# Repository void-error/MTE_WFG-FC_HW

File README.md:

# MTE_WFG-FC_HW
Waveform Generator + Frequency Counter hardware

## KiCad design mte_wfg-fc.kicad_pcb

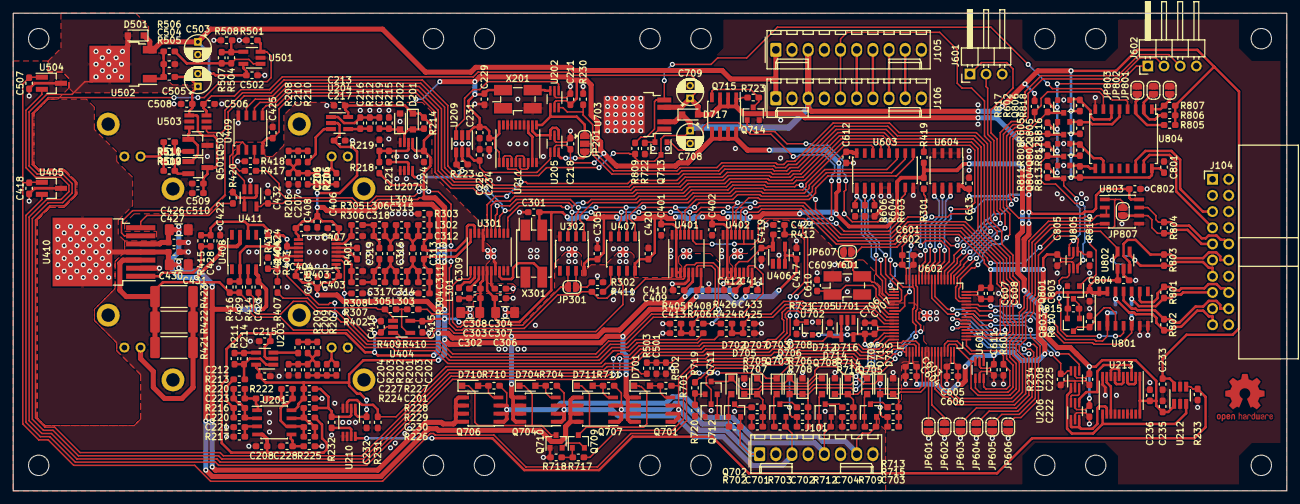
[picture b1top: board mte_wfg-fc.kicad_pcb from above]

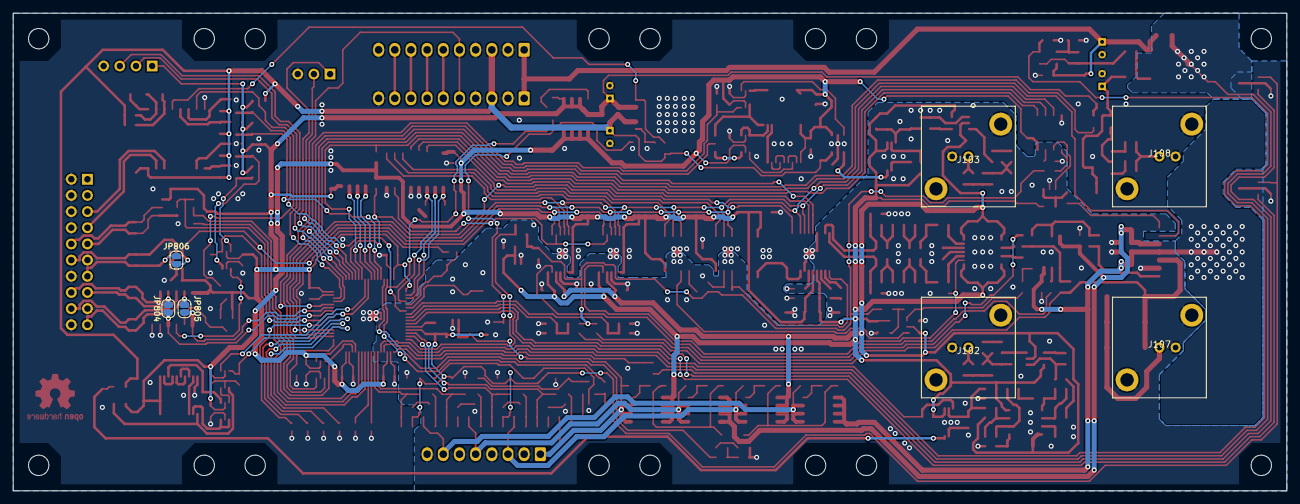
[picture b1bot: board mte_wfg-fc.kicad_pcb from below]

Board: 2 copper layers, 200.0 x 75.0 mm, 395 parts (7 on the bottom side), 222 nets.

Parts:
C201, C208, C211, C212, C213, C215, C217, C218, C222, C224, C225, C226, C229, C231, C232, C233, C234, C235, C236, C301, C303, C305, C307, C401, C402, C403, C404, C407, C408, C409, C410, C411, C412, C414, C415, C416, C418, C420, C422, C423, C425, C427, C430, C432, C502, C506, C507, C508, C509, C602, C603, C605, C607, C611, C612, C613, C801, C802, C803, C804, C805: 100n; C_0603_1608Metric_Pad1.05x0.95mm_HandSolder
C202, C205, C223, C230: 47p; C_0603_1608Metric_Pad1.05x0.95mm_HandSolder
C203, C206, C220, C227: 15p; C_0603_1608Metric_Pad1.05x0.95mm_HandSolder
C204, C207: 100p; C_0603_1608Metric_Pad1.05x0.95mm_HandSolder
C209, C210, C319: 33p; C_0603_1608Metric_Pad1.05x0.95mm_HandSolder
C214, C216, C221, C228, C310, C609, C610: 22p; C_0603_1608Metric_Pad1.05x0.95mm_HandSolder
C219, C304, C308, C309, C501, C701, C702, C703, C704, C707: 10n; C_0603_1608Metric_Pad1.05x0.95mm_HandSolder
C302, C306: 10u; C_1206_3216Metric_Pad1.42x1.75mm_HandSolder
C311, C312, C424, C429: 3p3; C_0603_1608Metric_Pad1.05x0.95mm_HandSolder
C313, C316: 56p; C_0603_1608Metric_Pad1.05x0.95mm_HandSolder
C314, C315: 10p; C_0603_1608Metric_Pad1.05x0.95mm_HandSolder
C317, C318: 6p8; C_0603_1608Metric_Pad1.05x0.95mm_HandSolder
C405, C406, C601, C604, C606, C608: 4u7; C_0603_1608Metric_Pad1.05x0.95mm_HandSolder
C413, C421, C428, C433: 1n; C_0603_1608Metric_Pad1.05x0.95mm_HandSolder
C417, C419, C504, C510, C705, C706: 1u; C_0603_1608Metric_Pad1.05x0.95mm_HandSolder
C426, C431: 1u; C_1206_3216Metric_Pad1.42x1.75mm_HandSolder
C503, C505, C708, C709: 10u; CP_Radial_D4.0mm_P2.00mm
D201, D202, D501, D717: BAS316; D_SOD-323_HandSoldering
D701, D702, D703, D704, D705, D706, D707, D708, D709, D710, D711, D712, D713, D714, D715, D716: BAT54J; D_SOD-323_HandSoldering
J101: MOLEX_KK-254; Molex_KK-254_AE-6410-08A_1x08_P2.54mm_Vertical
J102, J103, J107, J108: CONN_COAXIAL; TE_1-1337541-0
J104: Conn_02x10_Odd_Even; IDC-Header_2x10_P2.54mm_Horizontal
J105, J106: Conn_01x10; Molex_KK-254_AE-6410-10A_1x10_P2.54mm_Vertical
J601: Conn_01x03; PinHeader_1x03_P2.54mm_Horizontal
J602: Conn_01x04; PinHeader_1x04_P2.54mm_Horizontal
JP201: SolderJumper_3_Open; SolderJumper-3_P1.3mm_Open_RoundedPad1.0x1.5mm
JP301, JP601, JP602, JP603, JP604, JP605, JP606, JP607, JP801, JP802, JP803, JP804, JP805, JP806, JP807: SolderJumper_2_Open; SolderJumper-2_P1.3mm_Open_RoundedPad1.0x1.5mm
L301, L302: 3u3; L_0603_1608Metric_Pad1.05x0.95mm_HandSolder
L303, L304, L305, L306: 4u7; L_0603_1608Metric_Pad1.05x0.95mm_HandSolder
LOGO101: OSHW; OSHW-Logo2_9.8x8mm_Copper
MK101, MK102, MK103, MK104, MK105, MK106, MK107, MK108, MK109, MK110, MK111, MK112, MK113, MK114, MK115, MK116: mechanical:Mounting_Hole; MountingHole_3.2mm_M3
NT301, NT401, NT402, NT403, NT404, NT601: Net-Tie_4; NetTie-4_SMD_Pad0.5mm
Q501: BSS315P; SOT-23_Handsoldering
Q502: BSS316N; SOT-23_Handsoldering
Q701, Q707, Q715: IRF7241; SOIC-8_3.9x4.9mm_P1.27mm
Q702, Q708, Q803, Q805: BSS84; SOT-23
Q703, Q705, Q713, Q714, Q801, Q802, Q804, Q806: BSS138; SOT-23
Q704, Q706: IRF7468; SOIC-8_3.9x4.9mm_P1.27mm
Q709, Q711: BC847; SOT-23
Q710, Q712: BC857; SOT-23
R201, R204: 150k; R_0603_1608Metric_Pad1.05x0.95mm_HandSolder
R202, R205, R207, R208: 750; R_0603_1608Metric_Pad1.05x0.95mm_HandSolder
R203, R206, R223, R230, R231, R233, R234, R501, R504, R507, R601, R814: 100k; R_0603_1608Metric_Pad1.05x0.95mm_HandSolder
R209, R210: 150; R_0603_1608Metric_Pad1.05x0.95mm_HandSolder
R211, R212: 300R; R_0603_1608Metric_Pad1.05x0.95mm_HandSolder
R213, R216, R222, R224: 300; R_0603_1608Metric_Pad1.05x0.95mm_HandSolder
R214, R215, R218, R219, R227, R228: 1k5; R_0603_1608Metric_Pad1.05x0.95mm_HandSolder
R217, R225: 470; R_0603_1608Metric_Pad1.05x0.95mm_HandSolder
R220: 1k8; R_0603_1608Metric_Pad1.05x0.95mm_HandSolder
R221, R232, R714: 75k; R_0603_1608Metric_Pad1.05x0.95mm_HandSolder
R226: 2k; R_0603_1608Metric_Pad1.05x0.95mm_HandSolder
R229: 3k; R_0603_1608Metric_Pad1.05x0.95mm_HandSolder
R301, R602, R603, R604, R605, R606, R721, R805, R806, R807, R808, R809, R810, R811, R812, R813, R815, R816, R817, R818: 33k; R_0603_1608Metric_Pad1.05x0.95mm_HandSolder
R302, R715: 6k8; R_0603_1608Metric_Pad1.05x0.95mm_HandSolder
R303, R304, R305, R307, R413, R414: 200R; R_0603_1608Metric_Pad1.05x0.95mm_HandSolder
R306, R308: 51R; R_0603_1608Metric_Pad1.05x0.95mm_HandSolder
R401: 120R; R_0603_1608Metric_Pad1.05x0.95mm_HandSolder
R402, R415, R419: 10k; R_0603_1608Metric_Pad1.05x0.95mm_HandSolder
R403, R407, R412, R416: 1k; R_0603_1608Metric_Pad1.05x0.95mm_HandSolder
R404, R505: 750R; R_0603_1608Metric_Pad1.05x0.95mm_HandSolder
R405, R425: 2k7; R_0603_1608Metric_Pad1.05x0.95mm_HandSolder
R406, R424: 18k; R_0603_1608Metric_Pad1.05x0.95mm_HandSolder
R408, R426: 2k4; R_0603_1608Metric_Pad1.05x0.95mm_HandSolder
R409, R705, R707, R709, R710, R711, R712, R716: 15k; R_0603_1608Metric_Pad1.05x0.95mm_HandSolder
R410: 30k; R_0603_1608Metric_Pad1.05x0.95mm_HandSolder
R411: 24k; R_0603_1608Metric_Pad1.05x0.95mm_HandSolder
R417, R418, R502, R503: 5k1; R_0603_1608Metric_Pad1.05x0.95mm_HandSolder
R420: 3k9; R_0603_1608Metric_Pad1.05x0.95mm_HandSolder
R421, R422, R423: 150R; R_2512_6332Metric_Pad1.52x3.35mm_HandSolder
R506: 150R; R_0603_1608Metric_Pad1.05x0.95mm_HandSolder
R508: 47k; R_0603_1608Metric_Pad1.05x0.95mm_HandSolder
R509, R510, R511, R512, R801, R802, R803, R804: 100R; R_0603_1608Metric_Pad1.05x0.95mm_HandSolder
R701, R702, R703, R704, R717, R718, R719, R720, R722, R723: 3k3; R_0603_1608Metric_Pad1.05x0.95mm_HandSolder
R706: 13k; R_0603_1608Metric_Pad1.05x0.95mm_HandSolder
R708: 5k6; R_0603_1608Metric_Pad1.05x0.95mm_HandSolder
R713: 43k; R_0603_1608Metric_Pad1.05x0.95mm_HandSolder
U201: LT1819; SOIC-8_3.9x4.9mm_P1.27mm
U202, U208, U601, U805: 74LVC1G157; SOT-363_SC-70-6_Handsoldering
U203, U204: AD8065; SOT-23-5_HandSoldering
U205, U206: 74LVC2G14; SOT-363_SC-70-6_Handsoldering
U207, U210: AD8611; VSSOP-8_3.0x3.0mm_P0.65mm
U209, U212, U503: 74LVC1T45; SOT-23-6_Handsoldering
U211, U213: 74LVC273; TSSOP-20_4.4x6.5mm_P0.65mm
U301: AD9834; TSSOP-20_4.4x6.5mm_P0.65mm
U302, U407, U409: MCP41050; SOIC-8_3.9x4.9mm_P1.27mm
U401, U402: AD5721; TSSOP-16_4.4x5mm_P0.65mm
U403: LMH6503; TSSOP-14_4.4x5mm_P0.65mm
U404, U411, U501: TLV271; SOT-23-5_HandSoldering
U405, U504: MCP9700T-E/TT; SOT-23_Handsoldering
U406: LM4132-2; SOT-23-5_HandSoldering
U408: LT1363; SOIC-8_3.9x4.9mm_P1.27mm
U410: LMH6321; TO-263-7_TabPin8
U502: TLV1117-ADJ; TO-252-2
U602: STM32F101RCTx; LQFP-64_10x10mm_P0.5mm
U603: 74HC138; SOIC-16_3.9x9.9mm_P1.27mm
U604: 24LC04; SOIC-8_3.9x4.9mm_P1.27mm
U701: LM4132-3.3; SOT-23-5_HandSoldering
U702: STM809T; SOT-23
U703: NCP5661DT33; TO-252-4
U801: SN65MLVD203; SOIC-14_3.9x8.7mm_P1.27mm
U802: SN65LVDS2; SOT-23-5_HandSoldering
U803: SN65MLVD200A; SOIC-8_3.9x4.9mm_P1.27mm
U804: PCF8574; SOIC-16W_7.5x10.3mm_P1.27mm
X201: FOX924B-10.000; Crystal_SMD_EuroQuartz_MJ-4Pin_5.0x3.2mm_HandSoldering
X301: CFPS-73; Crystal_SMD_EuroQuartz_MQ-4Pin_7.0x5.0mm_HandSoldering
Y601: 16MHz; Crystal_SMD_EuroQuartz_MJ-4Pin_5.0x3.2mm_HandSoldering

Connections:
+3V3A: C418.2, C507.2, C702.2, C703.2, C706.2, C707.1, D706.1, D707.1, D713.1, D716.1, R708.1, R715.1, U405.1, U504.1, U602.13, U701.5, U702.3
+3V3D: C506.1, C601.2, C602.1, C603.1, C604.2, C605.1, C606.2, C607.1, C608.2, C611.1, C613.2, C709.1, C802.1, C803.1, C804.1, C805.1, D717.2, J602.1, Q715.1, Q715.2, Q715.3, Q803.2, Q805.2, R602.1, R605.2, R723.1, R808.2, R811.2, R815.2, U503.6, U601.2, U602.1, U602.19, U602.32, U602.48, U602.64, U604.8, U703.4, U801.13, U801.14, U802.1, U803.8, U805.2
+3V3P: C211.1, C218.1, C222.1, C225.1, C229.1, C231.2, C234.2, C235.2, C236.1, C301.1, C305.1, C306.1, C307.1, C401.1, C402.1, C420.1, C425.2, C612.1, Q715.5, Q715.6, Q715.7, Q715.8, R301.1, R419.1, U202.5, U205.5, U206.5, U208.5, U209.1, U211.1, U211.20, U212.1, U213.1, U213.20, U301.5, U302.8, U401.2, U401.3, U401.15, U402.2, U402.3, U402.15, U407.8, U409.8, U603.6, U603.16, X201.4, X301.4
+5V0A: C201.1, C212.1, C213.1, C224.2, C232.2, C302.1, C303.1, C308.1, C403.1, C404.1, C405.1, C409.1, C411.1, C415.1, C417.1, C432.2, D201.1, Q701.5, Q701.6, Q701.7, Q701.8, R214.1, R218.1, R227.1, U201.8, U203.5, U204.5, U207.1, U210.1, U301.4, U401.8, U402.8, U403.1, U403.14, U404.5, U406.3, U406.4, U411.5
+5V0D: C226.2, C233.2, C708.1, C801.1, D717.1, J105.3, J106.3, Q713.3, R805.1, R806.1, R807.1, R809.1, R812.1, R813.1, R816.1, R817.1, R818.1, U209.6, U212.6, U703.2, U804.16
+12V: C502.1, C503.1, D501.1, J105.1, J106.1, U501.5, U502.3
+15V: C422.2, C426.1, C427.1, Q707.5, Q707.6, Q707.7, Q707.8, U408.7, U410.5
-5V0A: C208.1, C215.1, C217.1, C406.1, C407.1, C408.1, C410.1, C412.2, C416.2, Q704.5, Q704.6, Q704.7, Q704.8, R229.2, U201.4, U203.2, U204.2, U401.6, U402.6, U403.7, U403.8, U404.2
-15V: C423.2, C430.1, C431.1, Q706.5, Q706.6, Q706.7, Q706.8, U408.4, U410.4, U410.8
/ADJ_SQR: R501.2, U501.3, U602.20
/Analog Output Stage/ANALOG_OUT: J107.1, R421.1, R422.1, R423.1
/Analog Output Stage/FB_NULL: C413.2, R405.2, R406.1, R408.1, U602.8
/Analog Output Stage/SIG_N: R305.1, R306.2, U403.6
/Analog Output Stage/SIG_P: R307.1, R308.2, U403.3
/Analog Output Stage/UMON_OUT: C433.1, R424.1, R425.1, R426.2, U602.9
/BUS_CLKR_N: J104.13, JP806.1, R803.2, U802.4
/BUS_CLKR_P: J104.12, R803.1, U802.3
/BUS_RX_N: J104.15, JP804.1, R801.2, U801.10
/BUS_RX_P: J104.16, R801.1, U801.9
/BUS_SCL: J104.5, U804.14
/BUS_SDA: J104.7, U804.15
/BUS_TRIG_N: J104.10, R804.2, U803.7
/BUS_TRIG_P: J104.9, JP807.1, R804.1, U803.6
/BUS_TX_N: J104.18, R802.2, U801.11
/BUS_TX_P: J104.19, JP805.1, R802.1, U801.12
/Bus Interface/BOOT0: Q805.3, R605.1, U602.60
/Bus Interface/CLKR: JP607.2, JP806.2, U802.5
/Bus Interface/EN_TX: R814.2, U602.41, U805.1
/Bus Interface/MCU_PG: R809.2, U703.5, U804.4
/Bus Interface/NRST: Q806.3, R602.2, U602.7
/Bus Interface/RX: JP805.2, U602.43, U801.2
/Bus Interface/TRIG_DIR: U602.28, U803.2, U803.3
/Bus Interface/TRIG_IN: U602.27, U803.4
/Bus Interface/TRIG_OUT: JP807.2, U602.26, U803.1
/Bus Interface/TX: JP804.2, U602.42, U801.5
/Control logic/ADJ_TRIG: R231.1, U210.3, U602.21
/Control logic/CS_A0: R606.1, U602.2, U603.1
/Control logic/CS_A1: R604.1, U602.3, U603.2
/Control logic/CS_A2: R603.1, U602.4, U603.3
/Control logic/DBG_RX: J601.1, U602.51
/Control logic/DBG_TX: J601.2, U602.52
/Control logic/DIV_SEL: R234.2, U208.6, U602.56
/Control logic/EN_PWR: Q714.1, R717.1, U602.62
/Control logic/EN_UMON: R719.1, U602.61
/Control logic/ID0: JP601.1, U602.24
/Control logic/ID1: JP602.1, U602.25
/Control logic/ID2: JP603.1, U602.37
/Control logic/ID3: JP604.1, U602.38
/Control logic/ID4: JP605.1, U602.39
/Control logic/ID5: JP606.1, U602.40
/Control logic/RCLK: JP201.2, U602.50
/Control logic/RCLK_SEL: R230.1, U202.6, U602.45
/Control logic/SCL: U602.58, U604.6
/Control logic/SDA: U602.59, U604.5
/Control logic/SWCLK: J602.3, U602.49
/Control logic/SWDIO: J602.2, U602.46
/Control logic/UMON_N5V0A: C702.1, D706.2, D708.1, R706.1, R708.2, U602.15
/Control logic/UMON_N15V: C703.1, D713.2, D715.1, R713.2, R715.2, U602.23
/Control logic/UMON_P5V0A: C701.2, D705.1, D707.2, R705.2, R707.2, U602.14
/Control logic/UMON_P15V: C704.1, D714.1, D716.2, R714.1, R716.1, U602.22
/Control logic/WP: U602.57, U604.7
/Digital Output Stage/DIGITAL_OUT: J108.1, R509.1, R510.2, R511.1, R512.2
/EF: R419.2, U410.6, U602.54
/Frequency Counter Input Stages/D0_R: U205.4, U211.3
/Frequency Counter Input Stages/D0_S: U206.4, U213.3
/Frequency Counter Input Stages/D1_R: U211.2, U211.4
/Frequency Counter Input Stages/D1_S: U213.2, U213.4
/Frequency Counter Input Stages/D2_R: U211.5, U211.7
/Frequency Counter Input Stages/D2_S: U213.5, U213.7
/Frequency Counter Input Stages/D3_R: U211.6, U211.8
/Frequency Counter Input Stages/D3_S: U213.6, U213.8
/Frequency Counter Input Stages/D4_R: U211.9, U211.13
/Frequency Counter Input Stages/D4_S: U213.9, U213.13
/Frequency Counter Input Stages/RCLK_IN: C205.2, J103.1, R204.2
/Frequency Counter Input Stages/SIG: U208.4, U602.55
/Frequency Counter Input Stages/SIG_IN: C202.2, J102.1, R201.2
/LDAC: U401.11, U402.11, U603.7
/MISO: U401.10, U402.10, U602.35
/MOSI: U301.13, U302.3, U401.12, U402.12, U407.3, U409.3, U602.36
/PG: J105.5, J106.5, U602.44
/PWM: J105.7, J106.7
/Power Distribution/N5V0A: J101.3, Q703.2, Q704.1, Q704.2, Q704.3, R703.2, R704.2
/Power Distribution/N15V: J101.7, Q705.2, Q706.1, Q706.2, Q706.3, R709.2, R710.2
/Power Distribution/P5V0A: C705.1, J101.1, Q701.1, Q701.2, Q701.3, Q702.2, R701.1, R702.2, U701.3, U701.4
/Power Distribution/P15V: J101.5, Q707.1, Q707.2, Q707.3, Q708.2, R711.1, R712.1
/RESET: R301.2, U301.11, U602.53
/RPM0: J105.8, J106.8
/RPM1: J105.9, J106.9
/SCLK: U301.14, U302.2, U401.14, U402.14, U407.2, U409.2, U602.34
/SIG_D: U503.4, U601.4
/SQR: U301.16, U601.3, U602.30
/SYNC: J105.6, J106.6
/TMON0: U504.2, U602.10
/TMON1: U405.2, U602.11
/UMON_SQR: C501.1, R502.1, R503.2, U602.17
/UMON_VREF: C421.2, R412.2, U602.16
/~ADJ_FS~: U302.1, U603.14
/~ADJ_NULL~: U407.1, U603.11
/~DAC_GAIN~: U401.13, U603.10
/~DAC_OFFSET~: U402.13, U603.9
/~DDS~: U301.15, U603.13
/~LVL_CL~: U409.1, U603.12
AGND: C201.2, C204.1, C207.1, C208.2, C212.2, C213.2, C215.2, C217.2, C221.2, C224.1, C228.2, C232.1, C302.2, C303.2, C304.2, C309.2, C403.2, C404.2, C405.2, C406.2, C407.2, C408.2, C409.2, C410.2, C411.2, C412.1, C413.1, C414.1, C415.2, C416.1, C417.2, C418.1, C419.2, C421.1, C422.1, C423.1, C426.2, C427.2, C430.2, C431.2, C432.1, C433.2, C501.2, C507.1, C609.2, C610.2, C701.1, C704.2, C705.2, C706.1, C707.2, D202.2, D705.2, D708.2, D714.2, D715.2, J101.2, J101.4, J101.6, J101.8, J102.2, J103.2, J107.2, NT301.2, NT301.4, NT401.2, NT401.4, NT402.2, NT402.4, NT403.2, NT403.4, NT404.2, NT404.4, NT601.1, NT601.3, Q710.1, Q712.1, R203.1, R206.1, R215.2, R217.2, R219.2, R225.2, R231.2, R302.2, R303.2, R304.2, R306.1, R308.1, R402.2, R405.1, R418.1, R425.2, R502.2, R707.1, R716.2, R718.2, R720.2, R721.1, U207.4, U207.5, U207.6, U210.4, U210.5, U210.6, U301.17, U301.18, U401.5, U402.5, U403.9, U403.11, U405.3, U406.2, U407.7, U410.2, U411.2, U504.3, U602.12, U701.2, U702.1, Y601.2, Y601.4
DGND: C211.2, C218.2, C222.2, C225.2, C226.1, C229.2, C231.1, C233.1, C234.1, C235.1, C236.2, C301.2, C305.2, C306.2, C307.2, C401.2, C402.2, C420.2, C425.1, C502.2, C503.2, C504.1, C505.2, C506.2, C508.2, C509.1, C510.1, C601.1, C602.2, C603.2, C604.1, C605.2, C606.1, C607.2, C608.1, C611.2, C612.2, C613.1, C708.2, C709.2, C801.2, C802.2, C803.2, C804.2, C805.2, J104.2, J104.4, J104.6, J104.8, J104.11, J104.14, J104.17, J104.20, J105.2, J105.4, J105.10, J106.2, J106.4, J106.10, J108.2, J601.3, J602.4, JP601.2, JP602.2, JP603.2, JP604.2, JP605.2, JP606.2, JP801.2, JP802.2, JP803.2, NT301.1, NT301.3, NT401.1, NT401.3, NT402.1, NT402.3, NT403.1, NT403.3, NT404.1, NT404.3, NT601.2, NT601.4, Q502.3, Q714.2, Q801.2, Q802.2, Q804.2, Q806.2, R223.2, R230.2, R233.2, R234.1, R501.1, R508.1, R601.2, R603.2, R604.2, R606.2, R722.1, R810.1, R814.1, U202.2, U205.2, U206.2, U208.2, U209.2, U209.5, U211.10, U211.14, U211.17, U211.18, U212.2, U212.5, U213.10, U213.14, U213.17, U213.18, U301.7, U301.9, U301.10, U301.12, U302.4, U401.16, U402.16, U407.4, U409.4, U501.2, U503.2, U503.5, U601.5, U602.18, U602.31, U602.47, U602.63, U603.4, U603.5, U603.8, U604.1, U604.2, U604.3, U604.4, U703.3, U801.6, U801.7, U802.2, U803.5, U804.8, U805.5, X201.2, X301.2
unnamed: C202.1, C203.2, R201.1, R202.2
unnamed: C203.1, C204.2, C209.2, R202.1, R203.2, R207.2
unnamed: C205.1, C206.2, R204.1, R205.2
unnamed: C206.1, C207.2, C210.2, R205.1, R206.2, R208.2
unnamed: C209.1, R207.1, R209.2
unnamed: C210.1, R208.1, R210.2
unnamed: C214.1, R211.1, R213.2, U203.1
unnamed: C214.2, R211.2, U203.4
unnamed: C216.1, C219.1, R212.1, U204.1
unnamed: C216.2, R212.2, U204.4
unnamed: C219.2, D201.2, D202.1, R214.2, R215.1, U207.3
unnamed: C220.1, C223.2, R216.1, R220.2, U201.2
unnamed: C220.2, R213.1, R216.2
unnamed: C221.1, R217.1, U201.3
unnamed: C223.1, R220.1, R222.2, U201.1
unnamed: C227.1, C230.2, R224.1, R226.2, U201.6
unnamed: C227.2, R222.1, R224.2
unnamed: C228.1, R225.1, U201.5
unnamed: C230.1, R226.1, R228.2, R229.1, U201.7
unnamed: C304.1, U301.6
unnamed: C308.2, U301.3
unnamed: C309.1, U301.2
unnamed: C310.1, C311.1, L301.1, R304.1, U301.20
unnamed: C310.2, C312.1, L302.2, R303.1, U301.19
unnamed: C311.2, C313.1, C314.1, L301.2, L303.1
unnamed: C312.2, C313.2, C315.1, L302.1, L304.2
unnamed: C314.2, C316.1, C317.1, L303.2, L305.1
unnamed: C315.2, C316.2, C318.1, L304.1, L306.2
unnamed: C317.2, C319.1, L305.2, R307.2
unnamed: C318.2, C319.2, L306.1, R305.2
unnamed: C414.2, R403.2, R407.1
unnamed: C424.1, C428.2, R415.2, U408.6
unnamed: C424.2, C429.2, R413.1, R416.2, U408.2
unnamed: C428.1, R415.1, U410.1
unnamed: C429.1, R416.1, R421.2, R422.2, R423.2, R424.2, U410.3
unnamed: C504.2, R505.2, R506.1, U502.1
unnamed: C505.1, C508.1, C509.2, C510.2, D501.2, Q501.3, R503.1, R505.1, U502.2, U503.1
unnamed: C609.1, JP607.1, U602.5, Y601.3
unnamed: C610.1, U602.6, Y601.1
unnamed: D701.1, D711.1, Q709.3
unnamed: D701.2, Q701.4, R701.2
unnamed: D702.1, D712.1, Q711.3
unnamed: D702.2, Q702.1, R702.1
unnamed: D703.1, D709.1, Q712.3
unnamed: D703.2, Q703.1, R703.1
unnamed: D704.1, D710.1, Q710.3
unnamed: D704.2, Q704.4, R704.1
unnamed: D709.2, Q705.1, R709.1
unnamed: D710.2, Q706.4, R710.1
unnamed: D711.2, Q707.4, R711.2
unnamed: D712.2, Q708.1, R712.2
unnamed: JP201.1, U202.4, U211.11
unnamed: JP201.3, U205.6
unnamed: JP301.1, U301.1, U302.6
unnamed: JP301.2, R302.1, U302.7
unnamed: JP801.1, R807.2, U804.1
unnamed: JP802.1, R806.2, U804.2
unnamed: JP803.1, R805.2, U804.3
unnamed: Q501.1, Q502.1, U503.3
unnamed: Q501.2, R509.2, R511.2
unnamed: Q502.2, R510.1, R512.1
unnamed: Q702.3, R705.1
unnamed: Q703.3, R706.2
unnamed: Q705.3, R713.1
unnamed: Q708.3, R714.2
unnamed: Q709.1, R717.2, R718.1
unnamed: Q709.2, Q710.2
unnamed: Q711.1, R719.2, R720.1
unnamed: Q711.2, Q712.2
unnamed: Q713.1, R721.2, U702.2
unnamed: Q713.2, R722.2, U703.1
unnamed: Q714.3, Q715.4, R723.2
unnamed: Q801.1, R817.2, U804.7
unnamed: Q801.3, Q803.1, R815.1
unnamed: Q802.1, R812.2, U804.10
unnamed: Q802.3, R808.1, U805.6
unnamed: Q803.3, R810.2, U801.3
unnamed: Q804.1, R813.2, U804.9
unnamed: Q804.3, R811.1, U805.3
unnamed: Q805.1, R816.2, U804.5
unnamed: Q806.1, R818.2, U804.6
unnamed: R209.1, U203.3
unnamed: R210.1, U204.3
unnamed: R218.2, R219.1, R221.2, U207.2
unnamed: R221.1, U207.7
unnamed: R223.1, U207.8, U209.4
unnamed: R227.2, R228.1, R232.2, U210.2
unnamed: R232.1, U210.7
unnamed: R233.1, U210.8, U212.4
unnamed: R401.1, U403.4
unnamed: R401.2, U403.5
unnamed: R402.1, U401.7, U403.2
unnamed: R403.1, R404.1, U403.12
unnamed: R404.2, R406.2, R413.2, U403.10
unnamed: R407.2, R409.1, U404.1
unnamed: R409.2, R410.1, U404.4
unnamed: R411.1, U407.5
unnamed: R414.1, U402.7
unnamed: R414.2, U408.3
unnamed: R417.1, U409.5
unnamed: R418.2, U409.7
unnamed: R420.1, U410.7
unnamed: R420.2, U411.1, U411.4
unnamed: R504.1, R507.1, R508.2, U501.4
unnamed: R504.2, R506.2, R507.2, U501.1
unnamed: R601.1, U601.6, U602.33
unnamed: U202.1, U209.3
unnamed: U202.3, X201.3
unnamed: U205.1, U205.3, U211.12
unnamed: U206.1, U206.3, U213.12
unnamed: U206.6, U208.3
unnamed: U208.1, U212.3, U213.11
unnamed: U301.8, X301.3
unnamed: U404.3, U407.6
unnamed: U409.6, U411.3
unnamed: U601.1, U602.29
unnamed: U801.4, U805.4
VREF: C419.1, R408.2, R410.2, R411.2, R412.1, R417.2, R426.1, U401.4, U402.4, U406.5

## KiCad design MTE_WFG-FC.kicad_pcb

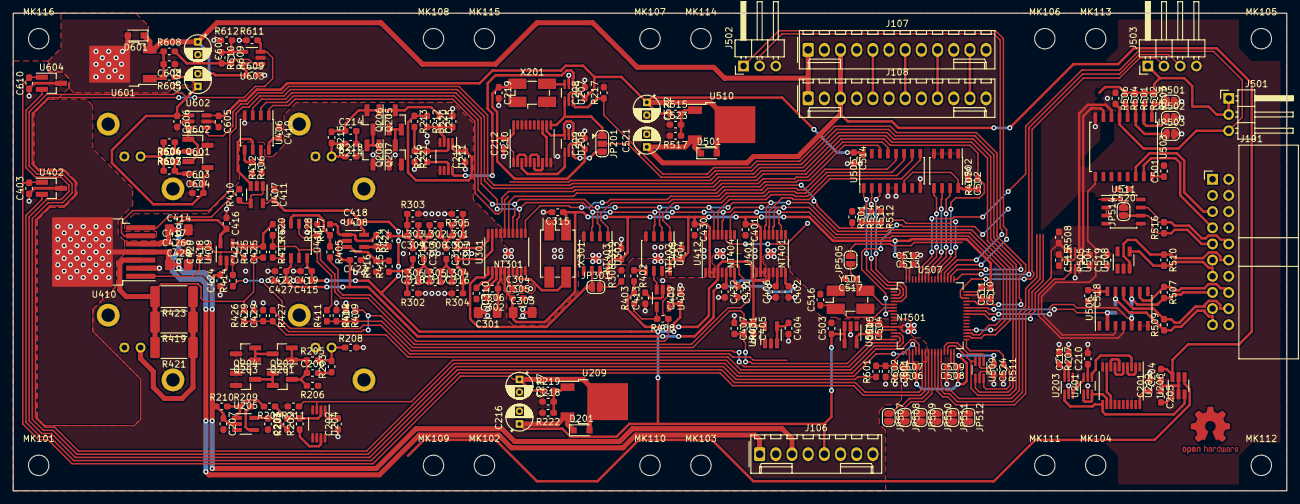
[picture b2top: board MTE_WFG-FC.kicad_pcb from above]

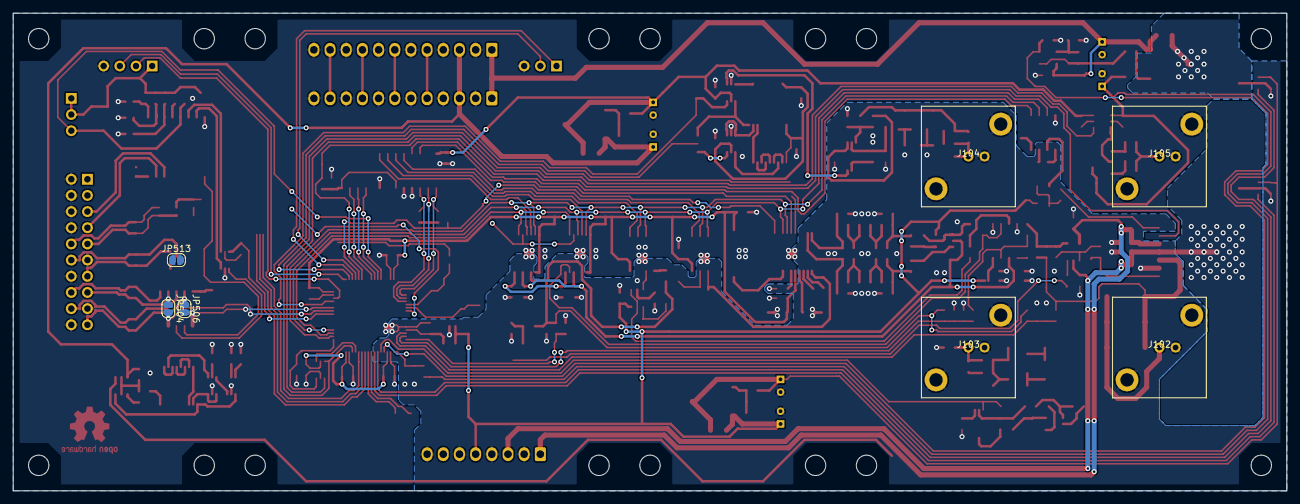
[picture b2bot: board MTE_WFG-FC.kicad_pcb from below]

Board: 2 copper layers, 200.0 x 75.0 mm, 302 parts (7 on the bottom side), 172 nets.

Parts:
C201, C202, C203, C204, C205, C207, C208, C209, C210, C211, C212, C213, C219, C302, C305, C315, C319, C401, C402, C403, C406, C408, C409, C410, C411, C413, C416, C417, C418, C419, C422, C423, C424, C426, C430, C431, C432, C501, C502, C506, C508, C510, C512, C514, C515, C518, C519, C520, C524, C603, C605, C606, C609, C610: 100n; C_0603_1608Metric_Pad1.05x0.95mm_HandSolder
C206, C214, C311, C516, C517: 22p; C_0603_1608Metric_Pad1.05x0.95mm_HandSolder
C215, C304, C306, C310, C505, C601: 10n; C_0603_1608Metric_Pad1.05x0.95mm_HandSolder
C216, C217, C521, C522, C602, C607: 10u; CP_Radial_D4.0mm_P2.00mm
C218, C404, C405, C415, C427, C503, C504, C523, C604, C608: 1u; C_0603_1608Metric_Pad1.05x0.95mm_HandSolder
C301, C303: 10u; C_1206_3216Metric_Pad1.42x1.75mm_HandSolder
C307, C316, C421, C425: 3p3; C_0603_1608Metric_Pad1.05x0.95mm_HandSolder
C308, C317: 10p; C_0603_1608Metric_Pad1.05x0.95mm_HandSolder
C309, C318: 6p8; C_0603_1608Metric_Pad1.05x0.95mm_HandSolder
C312, C313: 56p; C_0603_1608Metric_Pad1.05x0.95mm_HandSolder
C314: 33p; C_0603_1608Metric_Pad1.05x0.95mm_HandSolder
C407, C412, C420, C429: 1n; C_0603_1608Metric_Pad1.05x0.95mm_HandSolder
C414, C428: 1u; C_1206_3216Metric_Pad1.42x1.75mm_HandSolder
C507, C509, C511, C513: 4u7; C_0603_1608Metric_Pad1.05x0.95mm_HandSolder
D201, D501, D601: BAS316; D_SOD-323_HandSoldering
J101: Conn_02x10_Odd_Even; IDC-Header_2x10_P2.54mm_Horizontal
J102, J103, J104, J105: CONN_COAXIAL; TE_1-1337541-0
J106: MOLEX_KK-254; Molex_KK-254_AE-6410-08A_1x08_P2.54mm_Vertical
J107, J108: MOLEX_KK-254; Molex_KK-254_AE-6410-12A_1x12_P2.54mm_Vertical
J501, J502: Conn_01x03; PinHeader_1x03_P2.54mm_Horizontal
J503: Conn_01x04; PinHeader_1x04_P2.54mm_Horizontal
JP201: SolderJumper_3_Open; SolderJumper-3_P1.3mm_Open_RoundedPad1.0x1.5mm
JP301, JP501, JP502, JP503, JP504, JP505, JP506, JP507, JP508, JP509, JP510, JP511, JP512, JP513, JP514: SolderJumper_2_Open; SolderJumper-2_P1.3mm_Open_RoundedPad1.0x1.5mm
L301, L304: 3u3; L_0603_1608Metric_Pad1.05x0.95mm_HandSolder
L302, L303, L305, L306: 4u7; L_0603_1608Metric_Pad1.05x0.95mm_HandSolder
LOGO101: OSHW; OSHW-Logo2_9.8x8mm_Copper
MK101, MK102, MK103, MK104, MK105, MK106, MK107, MK108, MK109, MK110, MK111, MK112, MK113, MK114, MK115, MK116: mechanical:Mounting_Hole; MountingHole_3.2mm_M3
NT301, NT401, NT402, NT403, NT404, NT501: Net-Tie_4; NetTie-4_SMD_Pad0.5mm
Q201, Q202, Q203, Q204, Q205, Q206, Q207, Q208: BCW60; SOT-23_Handsoldering
Q601: BSS315P; SOT-23_Handsoldering
Q602: BSS316N; SOT-23_Handsoldering
R201, R204, R213, R221: 1k5; R_0603_1608Metric_Pad1.05x0.95mm_HandSolder
R202: 75k; R_0603_1608Metric_Pad1.05x0.95mm_HandSolder
R203, R205, R208, R212, R214, R215, R218, R220: 1M; R_0603_1608Metric_Pad1.05x0.95mm_HandSolder
R206, R209, R222, R517: 300R; R_0603_1608Metric_Pad1.05x0.95mm_HandSolder
R207, R211, R217, R405, R508, R511, R609, R610, R611: 100k; R_0603_1608Metric_Pad1.05x0.95mm_HandSolder
R210: 3k; R_0603_1608Metric_Pad1.05x0.95mm_HandSolder
R216: 7k5; R_0603_1608Metric_Pad1.05x0.95mm_HandSolder
R219, R515: 180R; R_0603_1608Metric_Pad1.05x0.95mm_HandSolder
R301, R501, R502, R503, R504, R505, R506, R512, R513, R514: 33k; R_0603_1608Metric_Pad1.05x0.95mm_HandSolder
R302, R303: 220R; R_0603_1608Metric_Pad1.05x0.95mm_HandSolder
R304, R305, R414, R420: 200R; R_0603_1608Metric_Pad1.05x0.95mm_HandSolder
R306: 6k8; R_0603_1608Metric_Pad1.05x0.95mm_HandSolder
R401, R425: 1k; R_0603_1608Metric_Pad1.05x0.95mm_HandSolder
R402: 24k; R_0603_1608Metric_Pad1.05x0.95mm_HandSolder
R403: 30k; R_0603_1608Metric_Pad1.05x0.95mm_HandSolder
R404, R427: 2k4; R_0603_1608Metric_Pad1.05x0.95mm_HandSolder
R406, R412, R601, R602: 5k1; R_0603_1608Metric_Pad1.05x0.95mm_HandSolder
R407, R418, R428: 10k; R_0603_1608Metric_Pad1.05x0.95mm_HandSolder
R408: 15k; R_0603_1608Metric_Pad1.05x0.95mm_HandSolder
R409, R429: 2k7; R_0603_1608Metric_Pad1.05x0.95mm_HandSolder
R410: 3k9; R_0603_1608Metric_Pad1.05x0.95mm_HandSolder
R411, R426: 18k; R_0603_1608Metric_Pad1.05x0.95mm_HandSolder
R413: 33R; R_0603_1608Metric_Pad1.05x0.95mm_HandSolder
R415, R416: 1k1; R_0603_1608Metric_Pad1.05x0.95mm_HandSolder
R417: 390R; R_0603_1608Metric_Pad1.05x0.95mm_HandSolder
R419, R421, R423: 150R; R_2512_6332Metric_Pad1.52x3.35mm_HandSolder
R422, R424: 2k2; R_0603_1608Metric_Pad1.05x0.95mm_HandSolder
R507, R509, R510, R516, R603, R604, R606, R607: 100R; R_0603_1608Metric_Pad1.05x0.95mm_HandSolder
R605: 750R; R_0603_1608Metric_Pad1.05x0.95mm_HandSolder
R608: 150R; R_0603_1608Metric_Pad1.05x0.95mm_HandSolder
R612: 47k; R_0603_1608Metric_Pad1.05x0.95mm_HandSolder
U201, U208: 74LVC2G14; SOT-363_SC-70-6_Handsoldering
U202, U210: 74LVC273; TSSOP-20_4.4x6.5mm_P0.65mm
U203, U207, U504, U509: 74LVC1G157; SOT-363_SC-70-6_Handsoldering
U204, U211: AD8611; VSSOP-8_3.0x3.0mm_P0.65mm
U205: AD8065; SOT-23-5_HandSoldering
U206, U602: 74LVC1T45; SOT-23-6_Handsoldering
U209, U510, U601: TLV1117-ADJ; TO-252-2
U301: AD9834; TSSOP-20_4.4x6.5mm_P0.65mm
U302, U404, U406: MCP41050; SOIC-8_3.9x4.9mm_P1.27mm
U401, U412: AD5721; TSSOP-16_4.4x5mm_P0.65mm
U402, U604: MCP9700T-E/TT; SOT-23_Handsoldering
U403: LM4132-2; SOT-23-5_HandSoldering
U405: LM321; SOT-23-5_HandSoldering
U407, U408, U603: TLV271; SOT-23-5_HandSoldering
U409: LM7121; SOT-23-5_HandSoldering
U410: LMH6321; TO-263-7_TabPin8
U411: AD603; SOIC-8_3.9x4.9mm_P1.27mm
U501: LM4132-3.3; SOT-23-5_HandSoldering
U502: 24LC04; SOIC-8_3.9x4.9mm_P1.27mm
U503: PCF8574; SOIC-16W_7.5x10.3mm_P1.27mm
U505: 74HC138; SOIC-16_3.9x9.9mm_P1.27mm
U506: SN65MLVD203; SOIC-14_3.9x8.7mm_P1.27mm
U507: STM32F101RCTx; LQFP-64_10x10mm_P0.5mm
U508: SN65LVDS2; SOT-23-5_HandSoldering
U511: SN65MLVD200A; SOIC-8_3.9x4.9mm_P1.27mm
X201: FOX924B-10.000; Crystal_SMD_EuroQuartz_MJ-4Pin_5.0x3.2mm_HandSoldering
X301: CFPS-73; Crystal_SMD_EuroQuartz_MQ-4Pin_7.0x5.0mm_HandSoldering
Y501: 16MHz; Crystal_SMD_EuroQuartz_MJ-4Pin_5.0x3.2mm_HandSoldering

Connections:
+3V3A: C213.2, C217.1, C403.2, C610.2, D201.2, R212.1, R213.1, R219.1, U209.2, U211.1, U402.1, U604.1
+3V3D: C201.1, C205.2, C208.1, C209.1, C210.1, C211.1, C212.2, C219.1, C303.1, C305.1, C315.1, C319.1, C401.1, C408.1, C410.2, C430.1, C501.1, C502.2, C506.1, C507.2, C508.1, C509.2, C510.1, C511.2, C512.1, C513.2, C514.1, C515.1, C518.1, C519.1, C520.1, C522.1, C524.1, C605.1, D501.2, J501.1, J501.2, J503.1, R301.1, R407.1, R501.1, R502.1, R503.1, R504.1, R505.1, R515.1, U201.5, U202.1, U202.20, U203.5, U206.1, U207.5, U208.5, U210.1, U210.20, U301.5, U302.8, U401.2, U401.3, U401.15, U404.8, U406.8, U412.2, U412.3, U412.15, U502.8, U503.16, U504.2, U505.6, U505.16, U506.13, U506.14, U507.1, U507.19, U507.32, U507.48, U507.64, U508.1, U509.2, U510.2, U511.8, U602.6, X201.4, X301.4
+5V0A: C202.2, C203.1, C216.1, C301.1, C302.1, C306.1, C402.1, C404.1, C409.1, C411.2, C415.1, C418.2, C419.1, C431.1, C503.1, D201.1, J106.5, R201.1, U204.1, U205.5, U209.3, U301.4, U401.8, U403.3, U403.4, U405.5, U407.5, U408.5, U411.8, U412.8, U501.3, U501.4
+5V0D: C204.2, C521.1, D501.1, J107.3, J108.3, U206.6, U510.3
+12V: C607.1, C609.1, D601.1, J107.1, J108.1, U601.3, U603.5
+15V: C414.1, C416.2, C417.1, J106.1, U409.5, U410.5
-5V0A: C207.1, C406.2, C413.2, C422.1, C423.2, C427.1, C432.1, J106.7, R210.1, U205.2, U401.6, U405.2, U408.2, U411.6, U412.6
-15V: C424.2, C426.1, C428.1, J106.3, U409.2, U410.4, U410.8
/ADJ_SQR: R611.2, U507.20, U603.3
/Analog Output Stage/ANALOG_OUT: J102.1, R419.1, R421.1, R423.1
/Analog Output Stage/FB_NULL: C412.2, R404.1, R409.2, R411.1, U507.15
/Analog Output Stage/SIG_N: C309.2, C314.1, L303.2, R303.1, R424.2
/Analog Output Stage/SIG_P: C314.2, C318.2, L306.1, R302.2, R415.1
/Analog Output Stage/UMON_OUT: C429.1, R426.1, R427.2, R429.1, U507.14
/BUS_CLKR_N: J101.13, JP513.1, R510.2, U508.4
/BUS_CLKR_P: J101.12, R510.1, U508.3
/BUS_RX_N: J101.15, JP504.1, R507.2, U506.10
/BUS_RX_P: J101.16, R507.1, U506.9
/BUS_SCL: J101.5, U503.14
/BUS_SDA: J101.7, U503.15
/BUS_TRIG_N: J101.10, R516.2, U511.7
/BUS_TRIG_P: J101.9, JP514.1, R516.1, U511.6
/BUS_TX_N: J101.18, R509.2, U506.11
/BUS_TX_P: J101.19, JP506.1, R509.1, U506.12
/Control logic/ADJ_TRIG: R211.1, U204.3, U507.21
/Control logic/BOOT0: J501.3, R506.2, U503.5, U507.60
/Control logic/CLKR: JP505.2, JP513.2, U508.5
/Control logic/CS_A0: R514.1, U505.1, U507.2
/Control logic/CS_A1: R513.1, U505.2, U507.3
/Control logic/CS_A2: R512.1, U505.3, U507.4
/Control logic/DBG_RX: J502.1, U507.51
/Control logic/DBG_TX: J502.2, U507.52
/Control logic/DIV_SEL: R207.2, U203.6, U507.56
/Control logic/ID0: JP507.1, U507.24
/Control logic/ID1: JP508.1, U507.25
/Control logic/ID2: JP509.1, U507.37
/Control logic/ID3: JP510.1, U507.38
/Control logic/ID4: JP511.1, U507.39
/Control logic/ID5: JP512.1, U507.40
/Control logic/NRST: R504.2, U503.4, U507.7
/Control logic/RCLK: JP201.2, U507.50
/Control logic/RCLK_SEL: R217.1, U207.6, U507.45
/Control logic/RX: JP506.2, U506.2, U507.43
/Control logic/RX_EN: U503.9, U506.3
/Control logic/SCL: U502.6, U507.58
/Control logic/SDA: U502.5, U507.59
/Control logic/SWCLK: J503.3, U507.49
/Control logic/SWDIO: J503.2, U507.46
/Control logic/TRIG_DIR: U507.28, U511.2, U511.3
/Control logic/TRIG_IN: U507.26, U511.4
/Control logic/TRIG_OUT: JP514.2, U507.27, U511.1
/Control logic/TX: JP504.2, U506.5, U507.42
/Control logic/TX_EN: U504.4, U506.4
/Control logic/WP: U502.7, U507.57
/Digital Output Stage/DIGITAL_OUT: J105.1, R603.1, R604.1, R606.2, R607.2
/EF: R407.2, U410.6, U507.54
/Frequency Counter Input Stages/D0_R: U208.4, U210.3
/Frequency Counter Input Stages/D0_S: U201.4, U202.3
/Frequency Counter Input Stages/D1_R: U210.2, U210.4
/Frequency Counter Input Stages/D1_S: U202.2, U202.4
/Frequency Counter Input Stages/D2_R: U210.5, U210.7
/Frequency Counter Input Stages/D2_S: U202.5, U202.7
/Frequency Counter Input Stages/D3_R: U210.6, U210.8
/Frequency Counter Input Stages/D3_S: U202.6, U202.8
/Frequency Counter Input Stages/D4_R: U210.9, U210.13
/Frequency Counter Input Stages/D4_S: U202.9, U202.13
/Frequency Counter Input Stages/RCLK_IN: J104.1, R214.2, R215.2, R218.1
/Frequency Counter Input Stages/SIG: U203.4, U507.55
/Frequency Counter Input Stages/SIG_IN: J103.1, R203.2, R205.2, R208.1
/LDAC: U401.11, U412.11, U505.7
/MISO: U401.10, U412.10, U507.35
/MOSI: U301.13, U302.3, U401.12, U404.3, U406.3, U412.12, U507.36
/PWM: J107.7, J108.7
/RESET: R301.2, U301.11, U507.53
/RPM0: J107.9, J108.9
/RPM1: J107.11, J108.11
/SCLK: U301.14, U302.2, U401.14, U404.2, U406.2, U412.14, U507.34
/SIG_D: U509.4, U602.4
/SQR: U301.16, U507.30, U509.3
/SYNC: J107.5, J108.5
/TMON0: U507.22, U604.2
/TMON1: U402.2, U507.23
/UMON_SQR: C601.1, R601.2, R602.1, U507.17
/UMON_VREF: C407.2, R401.2, U507.16
/~ADJ_FS~: U302.1, U505.12
/~ADJ_NULL~: U404.1, U505.11
/~DAC_GAIN~: U412.13, U505.10
/~DAC_OFFSET~: U401.13, U505.9
/~DDS~: U301.15, U505.14
/~LVL_CL~: U406.1, U505.13
AGND: C202.1, C203.2, C207.2, C213.1, C216.2, C217.2, C218.1, C301.2, C302.2, C304.2, C310.2, C402.2, C403.1, C404.2, C405.2, C406.1, C407.1, C409.2, C411.1, C412.1, C413.1, C414.2, C415.2, C416.1, C417.2, C418.1, C419.2, C422.2, C423.1, C424.1, C426.2, C427.2, C428.2, C429.2, C431.2, C432.2, C503.2, C504.1, C505.2, C601.2, C610.1, J102.2, J103.2, J104.2, J106.2, J106.4, J106.6, J106.8, NT301.2, NT301.4, NT401.2, NT401.4, NT402.2, NT402.4, NT403.2, NT403.4, NT404.2, NT404.4, NT501.1, NT501.3, Q203.3, Q204.1, Q204.2, Q207.3, Q208.1, Q208.2, R208.2, R211.2, R218.2, R220.2, R221.2, R222.2, R302.1, R303.2, R304.2, R305.2, R306.2, R409.1, R412.1, R416.1, R428.2, R429.2, R602.2, U204.4, U204.5, U204.6, U211.4, U211.5, U211.6, U301.17, U301.18, U401.5, U402.3, U403.2, U404.7, U407.2, U410.2, U411.1, U411.4, U412.5, U501.2, U507.12, U604.3
DGND: C201.2, C204.1, C205.1, C208.2, C209.2, C210.2, C211.2, C212.1, C219.2, C303.2, C305.2, C315.2, C319.2, C401.2, C408.2, C410.1, C430.2, C501.2, C502.1, C506.2, C507.1, C508.2, C509.1, C510.2, C511.1, C512.2, C513.1, C514.2, C515.2, C516.2, C517.2, C518.2, C519.2, C520.2, C521.2, C522.2, C523.1, C524.2, C602.2, C603.1, C604.1, C605.2, C606.2, C607.2, C608.1, C609.2, J101.2, J101.4, J101.6, J101.8, J101.11, J101.14, J101.17, J101.20, J105.2, J107.2, J107.4, J107.6, J107.8, J107.10, J107.12, J108.2, J108.4, J108.6, J108.8, J108.10, J108.12, J502.3, J503.4, JP501.2, JP502.2, JP503.2, JP507.2, JP508.2, JP509.2, JP510.2, JP511.2, JP512.2, NT301.1, NT301.3, NT401.1, NT401.3, NT402.1, NT402.3, NT403.1, NT403.3, NT404.1, NT404.3, NT501.2, NT501.4, Q602.3, R207.1, R217.2, R506.1, R508.1, R511.2, R512.2, R513.2, R514.2, R517.2, R611.1, R612.1, U201.2, U202.10, U202.14, U202.17, U202.18, U203.2, U206.2, U206.5, U207.2, U208.2, U210.10, U210.14, U210.17, U210.18, U301.7, U301.9, U301.10, U301.12, U302.4, U401.16, U404.4, U406.4, U412.16, U502.1, U502.2, U502.3, U502.4, U503.8, U504.5, U505.4, U505.5, U505.8, U506.6, U506.7, U507.18, U507.31, U507.47, U507.63, U508.2, U509.5, U511.5, U602.2, U602.5, U603.2, X201.2, X301.2, Y501.2, Y501.4
unnamed: C206.1, Q201.1, Q201.2, Q202.3, R205.1, R206.2
unnamed: C206.2, R203.1
unnamed: C214.1, C215.1, Q205.1, Q205.2, Q206.3, R215.1
unnamed: C214.2, R214.1
unnamed: C215.2, R212.2, R220.1, U211.3
unnamed: C218.2, R219.2, R222.1, U209.1
unnamed: C304.1, U301.6
unnamed: C306.2, U301.3
unnamed: C307.1, C311.1, L301.1, R305.1, U301.20
unnamed: C307.2, C308.1, C312.1, L301.2, L302.1
unnamed: C308.2, C309.1, C313.1, L302.2, L303.1
unnamed: C310.1, U301.2
unnamed: C311.2, C316.1, L304.2, R304.1, U301.19
unnamed: C312.2, C316.2, C317.1, L304.1, L305.2
unnamed: C313.2, C317.2, C318.1, L305.1, L306.2
unnamed: C420.1, R418.1, U410.1
unnamed: C420.2, C421.1, R418.2, U409.1
unnamed: C421.2, C425.2, R420.1, R425.2, U409.4
unnamed: C425.1, R419.2, R421.2, R423.2, R425.1, R426.2, U410.3
unnamed: C504.2, C505.1, U501.5, U507.13
unnamed: C516.1, U507.6, Y501.1
unnamed: C517.1, JP505.1, U507.5, Y501.3
unnamed: C523.2, R515.2, R517.1, U510.1
unnamed: C602.1, C603.2, C604.2, C606.1, D601.2, Q601.3, R601.1, R605.1, U601.2, U602.1
unnamed: C608.2, R605.2, R608.1, U601.1
unnamed: JP201.1, U207.4, U210.11
unnamed: JP201.3, U208.6
unnamed: JP301.1, U301.1, U302.6
unnamed: JP301.2, R306.1, U302.7
unnamed: JP501.1, R503.2, U503.1
unnamed: JP502.1, R502.2, U503.2
unnamed: JP503.1, R501.2, U503.3
unnamed: Q201.3, Q203.1, Q203.2
unnamed: Q202.1, Q202.2, Q204.3
unnamed: Q205.3, Q207.1, Q207.2
unnamed: Q206.1, Q206.2, Q208.3
unnamed: Q601.1, Q602.1, U602.3
unnamed: Q601.2, R603.2, R604.2
unnamed: Q602.2, R606.1, R607.1
unnamed: R201.2, R202.2, R204.1, U204.2
unnamed: R202.1, U204.7
unnamed: R204.2, R209.1, R210.2, U205.1
unnamed: R206.1, U205.3
unnamed: R209.2, U205.4
unnamed: R213.2, R216.2, R221.1, U211.2
unnamed: R216.1, U211.7
unnamed: R402.1, U404.5
unnamed: R403.1, R408.2, U405.4
unnamed: R405.1, R417.1, U411.3
unnamed: R405.2, R408.1, U405.1
unnamed: R406.1, U406.5
unnamed: R410.1, U407.1, U407.4
unnamed: R410.2, U410.7
unnamed: R411.2, R413.1, R420.2, U411.7
unnamed: R412.2, U406.7
unnamed: R413.2, U411.5
unnamed: R414.1, U401.7
unnamed: R414.2, U409.3
unnamed: R415.2, R416.2, U408.3
unnamed: R417.2, R422.1, U408.1
unnamed: R422.2, R424.1, U408.4
unnamed: R428.1, U411.2, U412.7
unnamed: R505.2, U503.7, U504.6
unnamed: R508.2, U504.3, U507.41
unnamed: R511.1, U507.33, U509.6
unnamed: R608.2, R609.2, R610.2, U603.1
unnamed: R609.1, R610.1, R612.2, U603.4
unnamed: U201.1, U201.3, U202.12
unnamed: U201.6, U203.3
unnamed: U202.11, U203.1, U206.3
unnamed: U204.8, U206.4
unnamed: U207.1, U211.8
unnamed: U207.3, X201.3
unnamed: U208.1, U208.3, U210.12
unnamed: U301.8, X301.3
unnamed: U404.6, U405.3
unnamed: U406.6, U407.3
unnamed: U503.6, U504.1
unnamed: U507.29, U509.1
VREF: C405.1, R401.1, R402.2, R403.2, R404.2, R406.2, R427.1, U401.4, U403.5, U412.4

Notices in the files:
mte_wfg-fc.kicad_pcb:
License: TAPR Open Hardware License - https://www.tapr.org/ohl
